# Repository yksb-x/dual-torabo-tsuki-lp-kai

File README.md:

# Dual-Torabo-Tsuki-LP改（仮）

torabo-tsuki lpは、せきごん氏によって設計された、トラックボール搭載の薄型（ロープロファイル）分割型ワイヤレスキーボードです。
本プロジェクトでは、この torabo-tsuki lp をより自分好みに最適化するため、PCB（プリント基板）の設計変更やケースの改造に取り組むことを目的としています。

## やりたい事
- 自分はMサイズを購入して使用しているが、Sサイズに近い構成で制作する。
- 電池のプラスマイナスを逆に取り付けられる様に配線を変更する。（縦型デザインの乾電池が正しい向きで見える様にする）
- トラックボールはデュアル前提とする。
- その上で、親指キーを左右３つずつ配置する
- トラックボールは19mm球を前提とする。
- ボトムプレート、トラボケースをケースと一体にして、高さ的にトラボが出っ張らない様にする。
- 電池カバーをもっと開閉しやすくする。（現状ノーアイデア）
- 持ち運び用のカバー（弁当箱みたいに上から被せる）
- テンティング（上記のカバーを左右逆にして底側から被せるとテンティングで使えます。みたいなやつ）

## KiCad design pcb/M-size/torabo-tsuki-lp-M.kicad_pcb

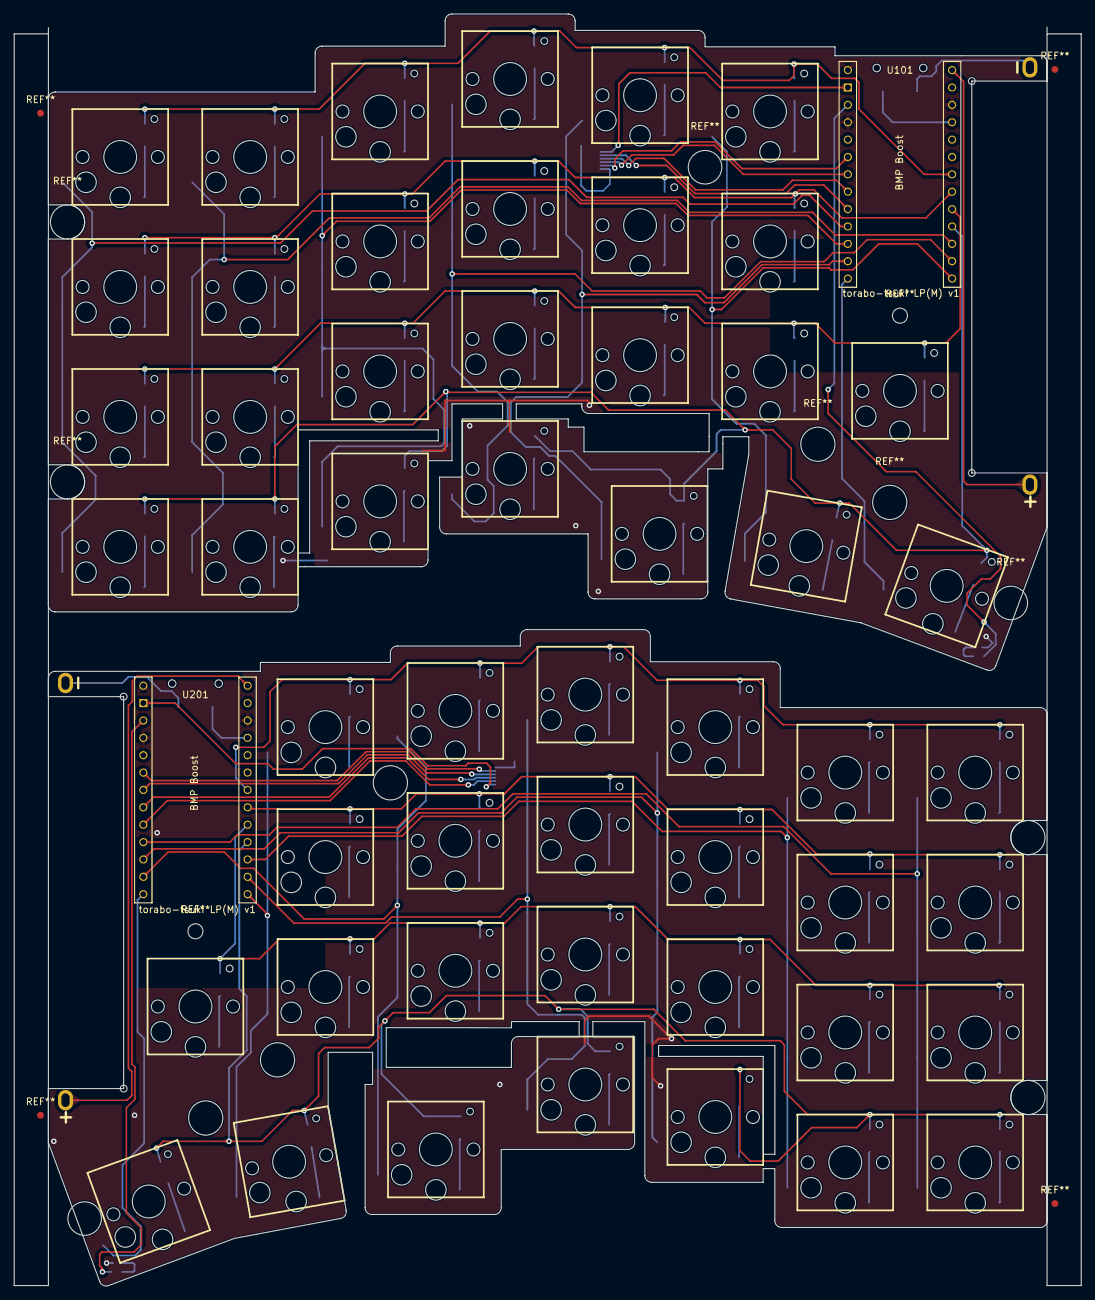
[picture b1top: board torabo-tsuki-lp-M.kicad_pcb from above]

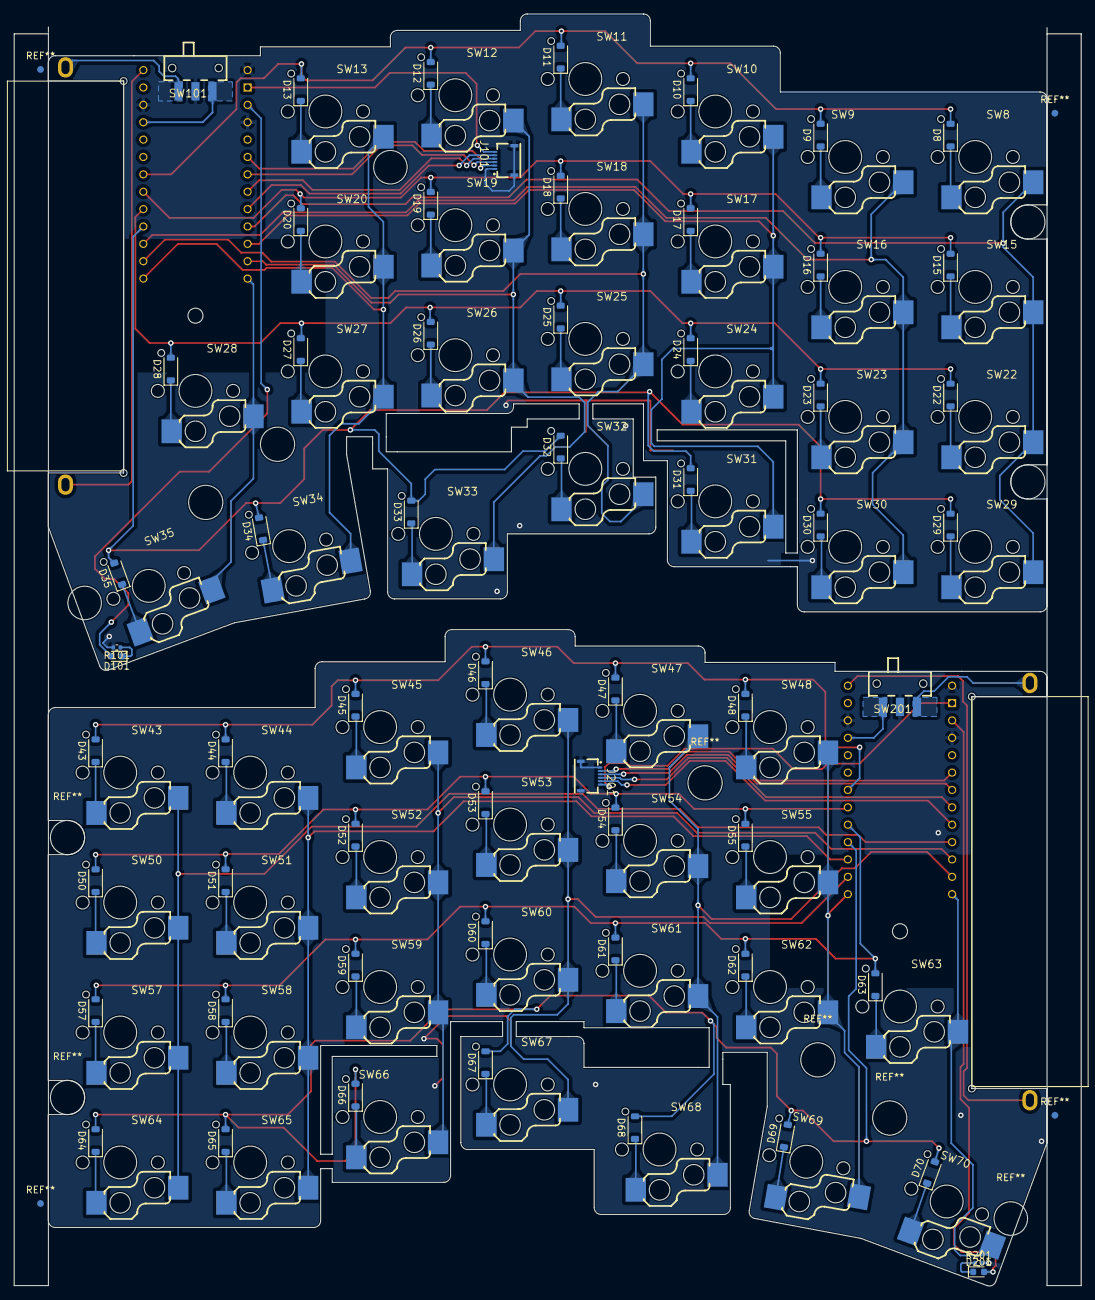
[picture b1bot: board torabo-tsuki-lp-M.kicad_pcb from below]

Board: 2 copper layers, 156.0 x 185.9 mm, 116 parts (114 on the bottom side), 93 nets.

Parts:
BT101, BT201: Battery_Cell; battery_holder
D8, D9, D10, D11, D12, D13, D15, D16, D17, D18, D19, D20, D22, D23, D24, D25, D26, D27, D28, D29, D30, D31, D32, D33, D34, D35, D43, D44, D45, D46, D47, D48, D50, D51, D52, D53, D54, D55, D57, D58, D59, D60, D61, D62, D63, D64, D65, D66, D67, D68, D69, D70: D_Small; D_SOD-123
D101, D201: LED_Small; LED_0603_1608Metric
J101, J201: Conn_01x06_MountingPin; GT-F0501SR10-06S1101
R101, R201: 330; R_0402_1005Metric
SW8, SW9, SW10, SW11, SW12, SW13, SW15, SW16, SW17, SW18, SW19, SW20, SW22, SW23, SW24, SW25, SW26, SW27, SW28, SW29, SW30, SW31, SW32, SW33, SW34, SW35, SW43, SW44, SW45, SW46, SW47, SW48, SW50, SW51, SW52, SW53, SW54, SW55, SW57, SW58, SW59, SW60, SW61, SW62, SW63, SW64, SW65, SW66, SW67, SW68, SW69, SW70: SW_Push; CHOC_V2_SOCKET_HANDSOLDERING
SW101, SW201: SW_SPDT; SW-SMD_K3-1280S-F1
U101, U201: BLEMicroPro

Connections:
+BATT: BT101.1 (+), BT201.1 (+), U101.26 (BAT), U201.26 (BAT)
/left/BOOT: SW101.3 (C), U101.23 (BOOT)
/left/COL0: SW8.1, SW15.1, SW22.1, SW29.1, U101.10 (22)
/left/COL1: SW9.1, SW16.1, SW23.1, SW30.1, U101.16 (47)
/left/COL2: SW10.1, SW17.1, SW24.1, SW31.1, U101.11 (23)
/left/COL3: SW11.1, SW18.1, SW25.1, SW32.1, U101.15 (10)
/left/COL4: SW12.1, SW19.1, SW26.1, SW33.1, U101.12 (32)
/left/COL5: SW13.1, SW20.1, SW27.1, SW34.1, U101.14 (9)
/left/COL6: SW28.1, SW35.1, U101.13 (35)
/left/CS: J101.5, U101.9 (20)
/left/LED: D101.2 (A), U101.3 (11)
/left/MOTION: J101.4, U101.8 (19)
/left/ROW1: D8.2 (A), D9.2 (A), D10.2 (A), D11.2 (A), D12.2 (A), D13.2 (A), U101.20 (0)
/left/ROW2: D15.2 (A), D16.2 (A), D17.2 (A), D18.2 (A), D19.2 (A), D20.2 (A), U101.19 (30)
/left/ROW3: D22.2 (A), D23.2 (A), D24.2 (A), D25.2 (A), D26.2 (A), D27.2 (A), D28.2 (A), U101.18 (3)
/left/ROW4: D29.2 (A), D30.2 (A), D31.2 (A), D32.2 (A), D33.2 (A), D34.2 (A), D35.2 (A), U101.17 (46)
/left/SCLK: J101.2, U101.6 (18)
/left/SDIO: J101.3, U101.7 (16)
/right/BOOT: SW201.1 (A), U201.23 (BOOT)
/right/COL0: SW43.1, SW50.1, SW57.1, SW64.1, U201.10 (22)
/right/COL1: SW44.1, SW51.1, SW58.1, SW65.1, U201.16 (47)
/right/COL2: SW45.1, SW52.1, SW59.1, SW66.1, U201.11 (23)
/right/COL3: SW46.1, SW53.1, SW60.1, SW67.1, U201.15 (10)
/right/COL4: SW47.1, SW54.1, SW61.1, SW68.1, U201.12 (32)
/right/COL5: SW48.1, SW55.1, SW62.1, SW69.1, U201.14 (9)
/right/COL6: SW63.1, SW70.1, U201.13 (35)
/right/CS: J201.5, U201.9 (20)
/right/LED: D201.2 (A), U201.3 (11)
/right/MOTION: J201.4, U201.8 (19)
/right/ROW1: D43.2 (A), D44.2 (A), D45.2 (A), D46.2 (A), D47.2 (A), D48.2 (A), U201.20 (0)
/right/ROW2: D50.2 (A), D51.2 (A), D52.2 (A), D53.2 (A), D54.2 (A), D55.2 (A), U201.19 (30)
/right/ROW3: D57.2 (A), D58.2 (A), D59.2 (A), D60.2 (A), D61.2 (A), D62.2 (A), D63.2 (A), U201.18 (3)
/right/ROW4: D64.2 (A), D65.2 (A), D66.2 (A), D67.2 (A), D68.2 (A), D69.2 (A), D70.2 (A), U201.17 (46)
/right/SCLK: J201.2, U201.6 (18)
/right/SDIO: J201.3, U201.7 (16)
GND: J101.1, J101.MP (MountPin), J201.1, J201.MP (MountPin), R101.2, R201.2, SW101.2 (B), SW201.2 (B), U101.1 (GND), U101.4 (GND), U101.24 (GND), U201.1 (GND), U201.4 (GND), U201.24 (GND)
unnamed: BT101.2 (-), SW101.1 (A)
unnamed: BT201.2 (-), SW201.3 (C)
unnamed: D8.1 (K), SW8.2
unnamed: D9.1 (K), SW9.2
unnamed: D10.1 (K), SW10.2
unnamed: D11.1 (K), SW11.2
unnamed: D12.1 (K), SW12.2
unnamed: D13.1 (K), SW13.2
unnamed: D15.1 (K), SW15.2
unnamed: D16.1 (K), SW16.2
unnamed: D17.1 (K), SW17.2
unnamed: D18.1 (K), SW18.2
unnamed: D19.1 (K), SW19.2
unnamed: D20.1 (K), SW20.2
unnamed: D22.1 (K), SW22.2
unnamed: D23.1 (K), SW23.2
unnamed: D24.1 (K), SW24.2
unnamed: D25.1 (K), SW25.2
unnamed: D26.1 (K), SW26.2
unnamed: D27.1 (K), SW27.2
unnamed: D28.1 (K), SW28.2
unnamed: D29.1 (K), SW29.2
unnamed: D30.1 (K), SW30.2
unnamed: D31.1 (K), SW31.2
unnamed: D32.1 (K), SW32.2
unnamed: D33.1 (K), SW33.2
unnamed: D34.1 (K), SW34.2
unnamed: D35.1 (K), SW35.2
unnamed: D43.1 (K), SW43.2
unnamed: D44.1 (K), SW44.2
unnamed: D45.1 (K), SW45.2
unnamed: D46.1 (K), SW46.2
unnamed: D47.1 (K), SW47.2
unnamed: D48.1 (K), SW48.2
unnamed: D50.1 (K), SW50.2
unnamed: D51.1 (K), SW51.2
unnamed: D52.1 (K), SW52.2
unnamed: D53.1 (K), SW53.2
unnamed: D54.1 (K), SW54.2
unnamed: D55.1 (K), SW55.2
unnamed: D57.1 (K), SW57.2
unnamed: D58.1 (K), SW58.2
unnamed: D59.1 (K), SW59.2
unnamed: D60.1 (K), SW60.2
unnamed: D61.1 (K), SW61.2
unnamed: D62.1 (K), SW62.2
unnamed: D63.1 (K), SW63.2
unnamed: D64.1 (K), SW64.2
unnamed: D65.1 (K), SW65.2
unnamed: D66.1 (K), SW66.2
unnamed: D67.1 (K), SW67.2
unnamed: D68.1 (K), SW68.2
unnamed: D69.1 (K), SW69.2
unnamed: D70.1 (K), SW70.2
unnamed: D101.1 (K), R101.1
unnamed: D201.1 (K), R201.1
VCC: J101.6, J201.6, U101.2 (8), U201.2 (8)

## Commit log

2025-10-21 Update key switch requirements in build guide
2025-10-29 Add instructions for firmware reset procedure in build guide
2025-12-19 Add LP(M) info
2025-12-31 Add L-size trackball image to README
2026-01-01 L-sizeのキー数追記
2026-01-10 シンプルケースを追加
2026-01-31 XSの情報を追加
2026-01-31 Add XS size controller cover STL files and update build guide with battery cover size information
2026-01-31 Update battery box soldering instructions and add installation image for AAA battery case
2026-02-05 Add XS size simple case STL files and update README with new images and descriptions
2026-02-10 ファームウェアの書き込み方法を追記
2026-02-21 破綻したメッシュを修正
2026-03-02 Add GitHub Actions workflow to close stale issues
2026-03-07 Add FAQ for USB connection issues with peripherals
    Added FAQ entry for USB connection issues with peripherals.
2026-03-21 Add troubleshooting checklist item for socket connection verification
2026-03-21 Add troubleshooting item for peripheral connection issues
2026-03-22 ミニトラックパッドの説明を追加
2026-03-27 Fix typo in mini-trackpad-option.md
2026-04-08 issueテンプレートを更新
2026-04-18 Enhance cutting instructions for bottom plate
    Added caution about cutting excess parts to avoid damaging wiring.
2026-05-02 Rename README.md to original_README.md
2026-05-02 Initialize README with project details and objectives
    Added project description and goals for Dual-Torabo-Tsuki-LP改.
2026-05-02 Enhance README with tenting cover description
    Add a note about the carrying cover design for tenting.
2026-05-02 Revise carrying cover and tenting descriptions
    Updated the descriptions for the carrying cover and tenting feature.
